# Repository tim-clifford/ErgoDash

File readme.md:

# ErgoDash-R

# Changes from original ErgoDash

- Added rotary encoder (scroll wheel) in place of the ErgoDash's optional outer thumb buttons
- Removed speaker to make pin available for rotary encoder
- Replaced firmware backlight control with physical toggle switch to make pin available for rotary encoder
- Replaced some parts with ones easier to obtain in the UK
- Added jumper pin positions for backlight switch and spare keyboard switch to allow adding functionality later

# Parts

[Parts List](https://github.com/tim-clifford/ErgoDash-R/tree/master/doc/shoplist.ods)

# Firmware

The ErgoDash-R uses QMK for its firmware. It will need updating from the original ErgoDash firmware here:
[QMK - ErgoDash directory](https://github.com/qmk/qmk_firmware/tree/master/keyboards/ergodash)
.  

# Build Guide

I will add a build guide once I have finished building mine! The original ErgoDash build guide is likely to be useful:

[ErgoDash Build Guide](https://github.com/omkbd/ErgoDash/blob/master/Doc/build-en.md)

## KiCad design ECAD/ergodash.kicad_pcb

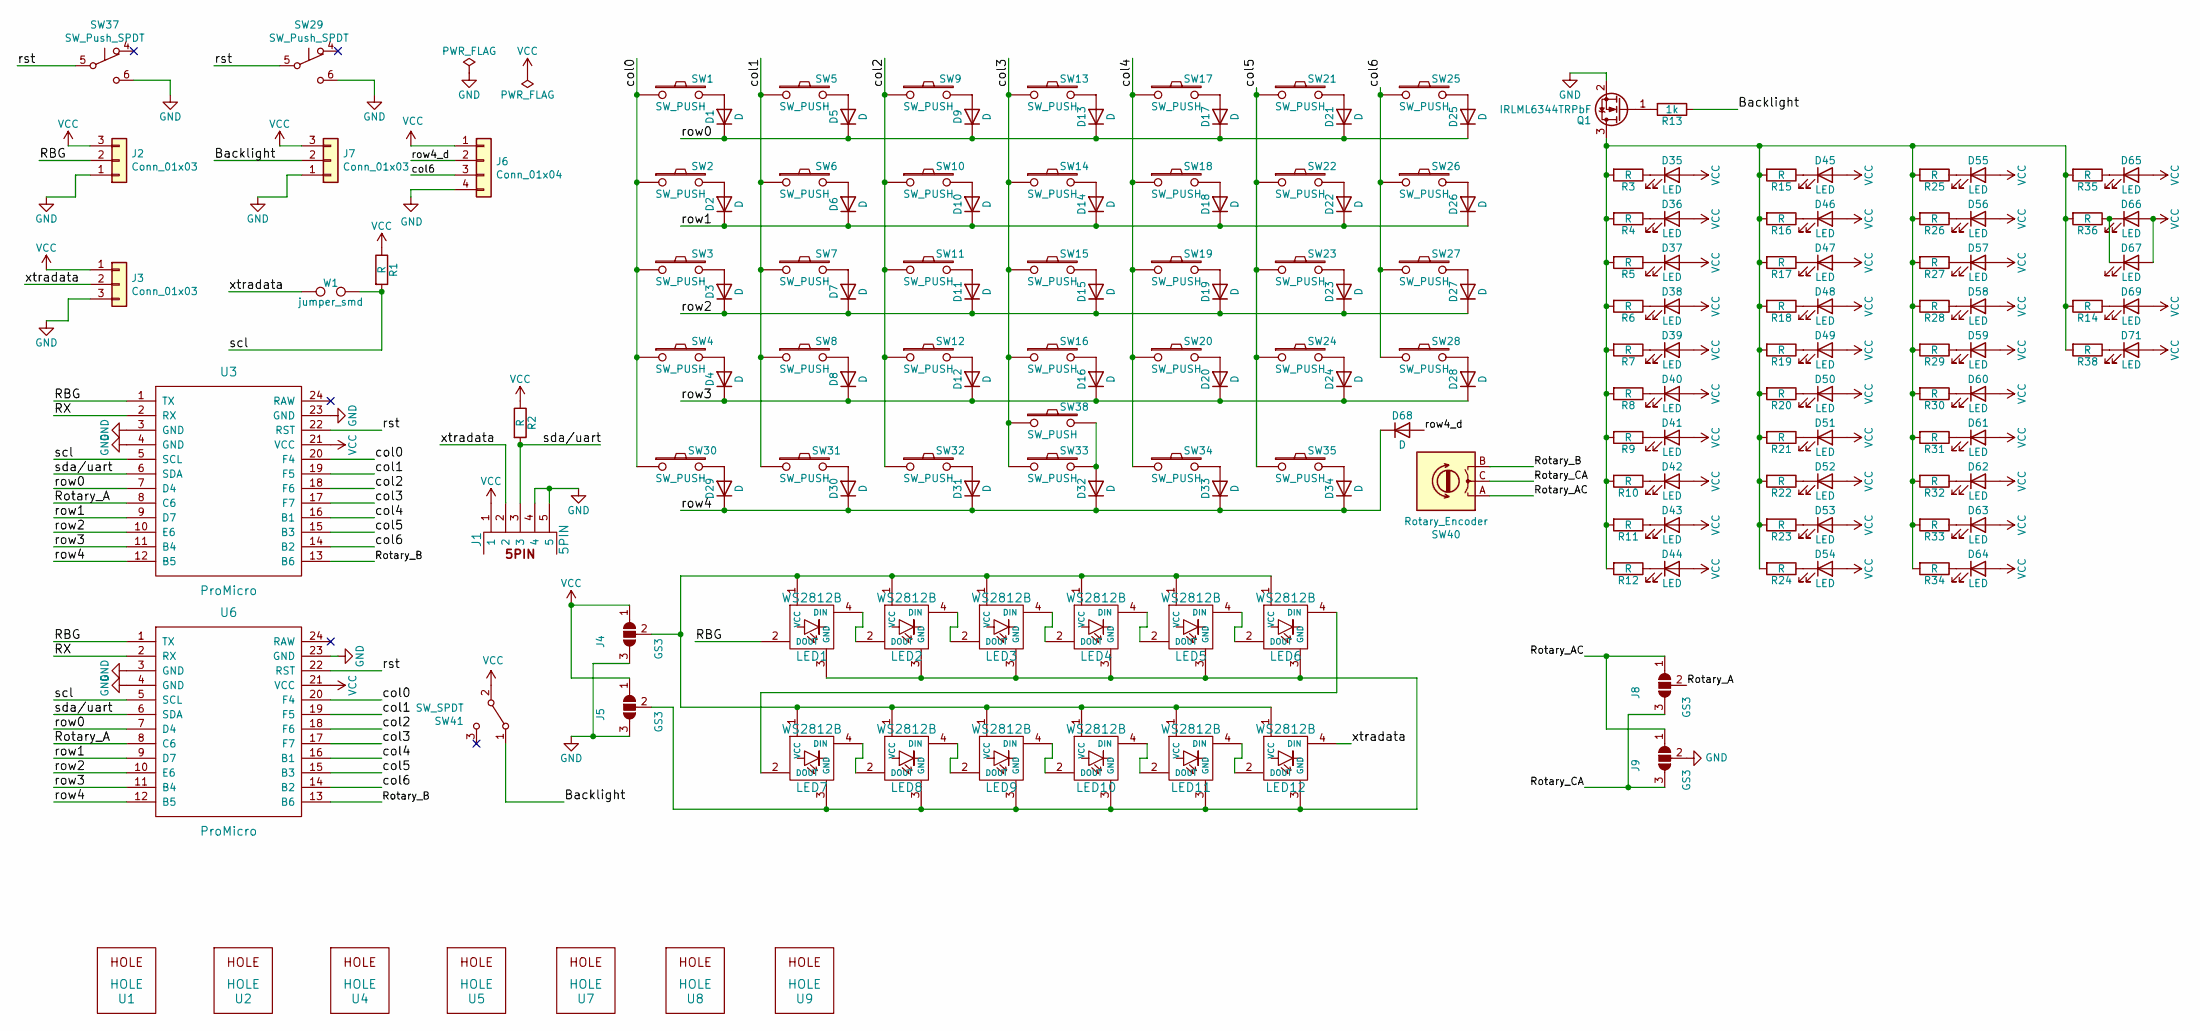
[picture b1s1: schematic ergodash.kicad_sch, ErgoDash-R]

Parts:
D1, D2, D3, D4, D5, D6, D7, D8, D9, D10, D11, D12, D13, D14, D15, D16, D17, D18, D19, D20, D21, D22, D23, D24, D25, D26, D27, D28, D29, D30, D31, D32, D33, D34, D68: D; Diode_SMD_THT3
D35, D36, D37, D38, D39, D40, D41, D42, D43, D44, D45, D46, D47, D48, D49, D50, D51, D52, D53, D54, D55, D56, D57, D58, D59, D60, D61, D62, D63, D64, D65, D66, D67, D69, D71: LED; CHERRY_MX_LED2
J1: 5PIN; trss_jack
J2, J3, J7: Conn_01x03; conn3
J4, J5, J8, J9: GS3; jumper2
J6: Conn_01x04; conn4
LED1, LED2, LED3, LED4, LED5, LED6, LED7, LED8, LED9, LED10, LED11, LED12: WS2812B; WS2812B-5
Q1: IRLML6344TRPbF; SOT-23_2
R1, R2: R; R_Axial_DIN0207_L6.3mm_D2.5mm_P10.16mm_Horizontal
R3, R4, R5, R6, R7, R8, R9, R10, R11, R12, R14, R15, R16, R17, R18, R19, R20, R21, R22, R23, R24, R25, R26, R27, R28, R29, R30, R31, R32, R33, R34, R35, R36, R38: R; Resistors_SMD_THT
R13: 1k; Resistors_SMD_THT
SW1, SW2, SW3, SW4, SW5, SW6, SW7, SW8, SW9, SW10, SW11, SW12, SW13, SW14, SW15, SW16, SW17, SW18, SW19, SW20, SW21, SW22, SW23, SW24, SW25, SW26, SW27, SW28, SW30, SW31, SW32, SW33, SW34, SW35, SW38: SW_PUSH; MX_ALPS
SW29, SW37: SW_Push_SPDT
SW40: Rotary_Encoder; Kailh_Encoder
SW41: SW_SPDT; MC2MS1T2B2M6RE
U1, U2, U4, U5, U7, U8, U9: HOLE; hole
U3, U6: ProMicro
W1: jumper_smd; jumper_smd_2dub

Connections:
/Backlight: J7.2, R13.1, SW41.1 (A)
/RBG: J2.2, LED1.2 (DOUT), U3.1 (TX), U6.1 (TX)
/RX: U3.2 (RX), U6.2 (RX)
/Rotary_A: J8.2 (C), U3.8 (C6), U6.8 (C6)
/Rotary_AC: J8.1 (A), J9.1 (A), SW40.A
/Rotary_B: SW40.B, U3.13 (B6), U6.13 (B6)
/Rotary_CA: J8.3 (B), J9.3 (B), SW40.C
/col0: SW1.1, SW2.1, SW3.1, SW4.1, SW30.1, U3.20 (F4), U6.20 (F4)
/col1: SW5.1, SW6.1, SW7.1, SW8.1, SW31.1, U3.19 (F5), U6.19 (F5)
/col2: SW9.1, SW10.1, SW11.1, SW12.1, SW32.1, U3.18 (F6), U6.18 (F6)
/col3: SW13.1, SW14.1, SW15.1, SW16.1, SW33.1, SW38.1, U3.17 (F7), U6.17 (F7)
/col4: SW17.1, SW18.1, SW19.1, SW20.1, SW34.1, U3.16 (B1), U6.16 (B1)
/col5: SW21.1, SW22.1, SW23.1, SW24.1, SW35.1, U3.15 (B3), U6.15 (B3)
/col6: J6.3, SW25.1, SW26.1, SW27.1, SW28.1, U3.14 (B2), U6.14 (B2)
/row0: D1.1 (K), D5.1 (K), D9.1 (K), D13.1 (K), D17.1 (K), D21.1 (K), D25.1 (K), U3.7 (D4), U6.7 (D4)
/row1: D2.1 (K), D6.1 (K), D10.1 (K), D14.1 (K), D18.1 (K), D22.1 (K), D26.1 (K), U3.9 (D7), U6.9 (D7)
/row2: D3.1 (K), D7.1 (K), D11.1 (K), D15.1 (K), D19.1 (K), D23.1 (K), D27.1 (K), U3.10 (E6), U6.10 (E6)
/row3: D4.1 (K), D8.1 (K), D12.1 (K), D16.1 (K), D20.1 (K), D24.1 (K), D28.1 (K), U3.11 (B4), U6.11 (B4)
/row4: D29.1 (K), D30.1 (K), D31.1 (K), D32.1 (K), D33.1 (K), D34.1 (K), D68.1 (K), U3.12 (B5), U6.12 (B5)
/row4_d: D68.2 (A), J6.2
/rst: SW29.5 (B), SW37.5 (B), U3.22 (RST), U6.22 (RST)
/scl: R1.2, U3.5 (SCL), U6.5 (SCL), W1.2
/sda/uart: J1.3, R2.2, U3.6 (SDA), U6.6 (SDA)
/xtradata: J1.2, J3.2, LED12.4 (DIN), W1.1
GND: J1.4, J1.5, J2.1, J3.3, J4.3 (B), J5.3 (B), J6.4, J7.1, J9.2 (C), Q1.2 (S), SW29.6 (C), SW37.6 (C), U3.3 (GND), U3.4 (GND), U3.23 (GND), U6.3 (GND), U6.4 (GND), U6.23 (GND)
unnamed: D1.2 (A), SW1.2
unnamed: D2.2 (A), SW2.2
unnamed: D3.2 (A), SW3.2
unnamed: D4.2 (A), SW4.2
unnamed: D5.2 (A), SW5.2
unnamed: D6.2 (A), SW6.2
unnamed: D7.2 (A), SW7.2
unnamed: D8.2 (A), SW8.2
unnamed: D9.2 (A), SW9.2
unnamed: D10.2 (A), SW10.2
unnamed: D11.2 (A), SW11.2
unnamed: D12.2 (A), SW12.2
unnamed: D13.2 (A), SW13.2
unnamed: D14.2 (A), SW14.2
unnamed: D15.2 (A), SW15.2
unnamed: D16.2 (A), SW16.2
unnamed: D17.2 (A), SW17.2
unnamed: D18.2 (A), SW18.2
unnamed: D19.2 (A), SW19.2
unnamed: D20.2 (A), SW20.2
unnamed: D21.2 (A), SW21.2
unnamed: D22.2 (A), SW22.2
unnamed: D23.2 (A), SW23.2
unnamed: D24.2 (A), SW24.2
unnamed: D25.2 (A), SW25.2
unnamed: D26.2 (A), SW26.2
unnamed: D27.2 (A), SW27.2
unnamed: D28.2 (A), SW28.2
unnamed: D29.2 (A), SW30.2
unnamed: D30.2 (A), SW31.2
unnamed: D31.2 (A), SW32.2
unnamed: D32.2 (A), SW33.2, SW38.2
unnamed: D33.2 (A), SW34.2
unnamed: D34.2 (A), SW35.2
unnamed: D35.1 (K), R3.1
unnamed: D36.1 (K), R4.1
unnamed: D37.1 (K), R5.1
unnamed: D38.1 (K), R6.1
unnamed: D39.1 (K), R7.1
unnamed: D40.1 (K), R8.1
unnamed: D41.1 (K), R9.1
unnamed: D42.1 (K), R10.1
unnamed: D43.1 (K), R11.1
unnamed: D44.1 (K), R12.1
unnamed: D45.1 (K), R15.1
unnamed: D46.1 (K), R16.1
unnamed: D47.1 (K), R17.1
unnamed: D48.1 (K), R18.1
unnamed: D49.1 (K), R19.1
unnamed: D50.1 (K), R20.1
unnamed: D51.1 (K), R21.1
unnamed: D52.1 (K), R22.1
unnamed: D53.1 (K), R23.1
unnamed: D54.1 (K), R24.1
unnamed: D55.1 (K), R25.1
unnamed: D56.1 (K), R26.1
unnamed: D57.1 (K), R27.1
unnamed: D58.1 (K), R28.1
unnamed: D59.1 (K), R29.1
unnamed: D60.1 (K), R30.1
unnamed: D61.1 (K), R31.1
unnamed: D62.1 (K), R32.1
unnamed: D63.1 (K), R33.1
unnamed: D64.1 (K), R34.1
unnamed: D65.1 (K), R35.1
unnamed: D66.1 (K), D67.1 (K), R36.1
unnamed: D69.1 (K), R14.1
unnamed: D71.1 (K), R38.1
unnamed: J4.2 (C), LED1.1 (VCC), LED2.1 (VCC), LED3.1 (VCC), LED4.1 (VCC), LED5.1 (VCC), LED6.1 (VCC), LED7.1 (VCC), LED8.1 (VCC), LED9.1 (VCC), LED10.1 (VCC), LED11.1 (VCC), LED12.1 (VCC)
unnamed: J5.2 (C), LED1.3 (GND), LED2.3 (GND), LED3.3 (GND), LED4.3 (GND), LED5.3 (GND), LED6.3 (GND), LED7.3 (GND), LED8.3 (GND), LED9.3 (GND), LED10.3 (GND), LED11.3 (GND), LED12.3 (GND)
unnamed: LED1.4 (DIN), LED2.2 (DOUT)
unnamed: LED2.4 (DIN), LED3.2 (DOUT)
unnamed: LED3.4 (DIN), LED4.2 (DOUT)
unnamed: LED4.4 (DIN), LED5.2 (DOUT)
unnamed: LED5.4 (DIN), LED6.2 (DOUT)
unnamed: LED6.4 (DIN), LED7.2 (DOUT)
unnamed: LED7.4 (DIN), LED8.2 (DOUT)
unnamed: LED8.4 (DIN), LED9.2 (DOUT)
unnamed: LED9.4 (DIN), LED10.2 (DOUT)
unnamed: LED10.4 (DIN), LED11.2 (DOUT)
unnamed: LED11.4 (DIN), LED12.2 (DOUT)
unnamed: Q1.1 (G), R13.2
unnamed: Q1.3 (D), R3.2, R4.2, R5.2, R6.2, R7.2, R8.2, R9.2, R10.2, R11.2, R12.2, R14.2, R15.2, R16.2, R17.2, R18.2, R19.2, R20.2, R21.2, R22.2, R23.2, R24.2, R25.2, R26.2, R27.2, R28.2, R29.2, R30.2, R31.2, R32.2, R33.2, R34.2, R35.2, R36.2, R38.2
VCC: D35.2 (A), D36.2 (A), D37.2 (A), D38.2 (A), D39.2 (A), D40.2 (A), D41.2 (A), D42.2 (A), D43.2 (A), D44.2 (A), D45.2 (A), D46.2 (A), D47.2 (A), D48.2 (A), D49.2 (A), D50.2 (A), D51.2 (A), D52.2 (A), D53.2 (A), D54.2 (A), D55.2 (A), D56.2 (A), D57.2 (A), D58.2 (A), D59.2 (A), D60.2 (A), D61.2 (A), D62.2 (A), D63.2 (A), D64.2 (A), D65.2 (A), D66.2 (A), D67.2 (A), D69.2 (A), D71.2 (A), J1.1, J2.3, J3.1, J4.1 (A), J5.1 (A), J6.1, J7.3, R1.1, R2.1, SW41.2 (B), U3.21 (VCC), U6.21 (VCC)
no_connect_110: SW29.4 (A)
no_connect_111: SW37.4 (A)
no_connect_112: SW41.3 (C)
no_connect_113: U3.24 (RAW)
no_connect_114: U6.24 (RAW)

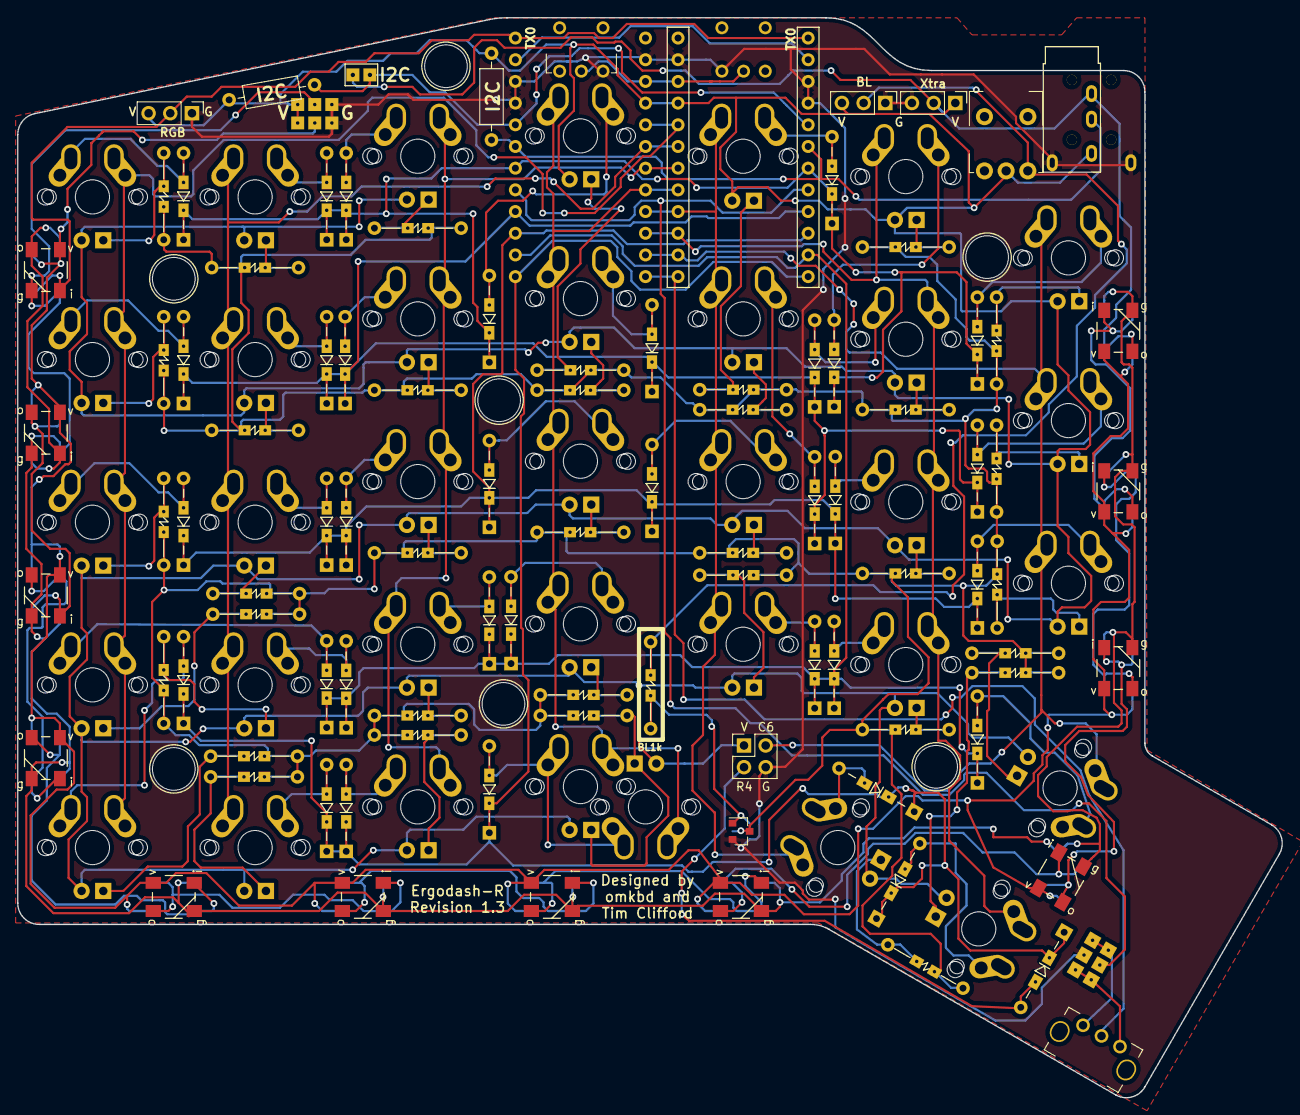
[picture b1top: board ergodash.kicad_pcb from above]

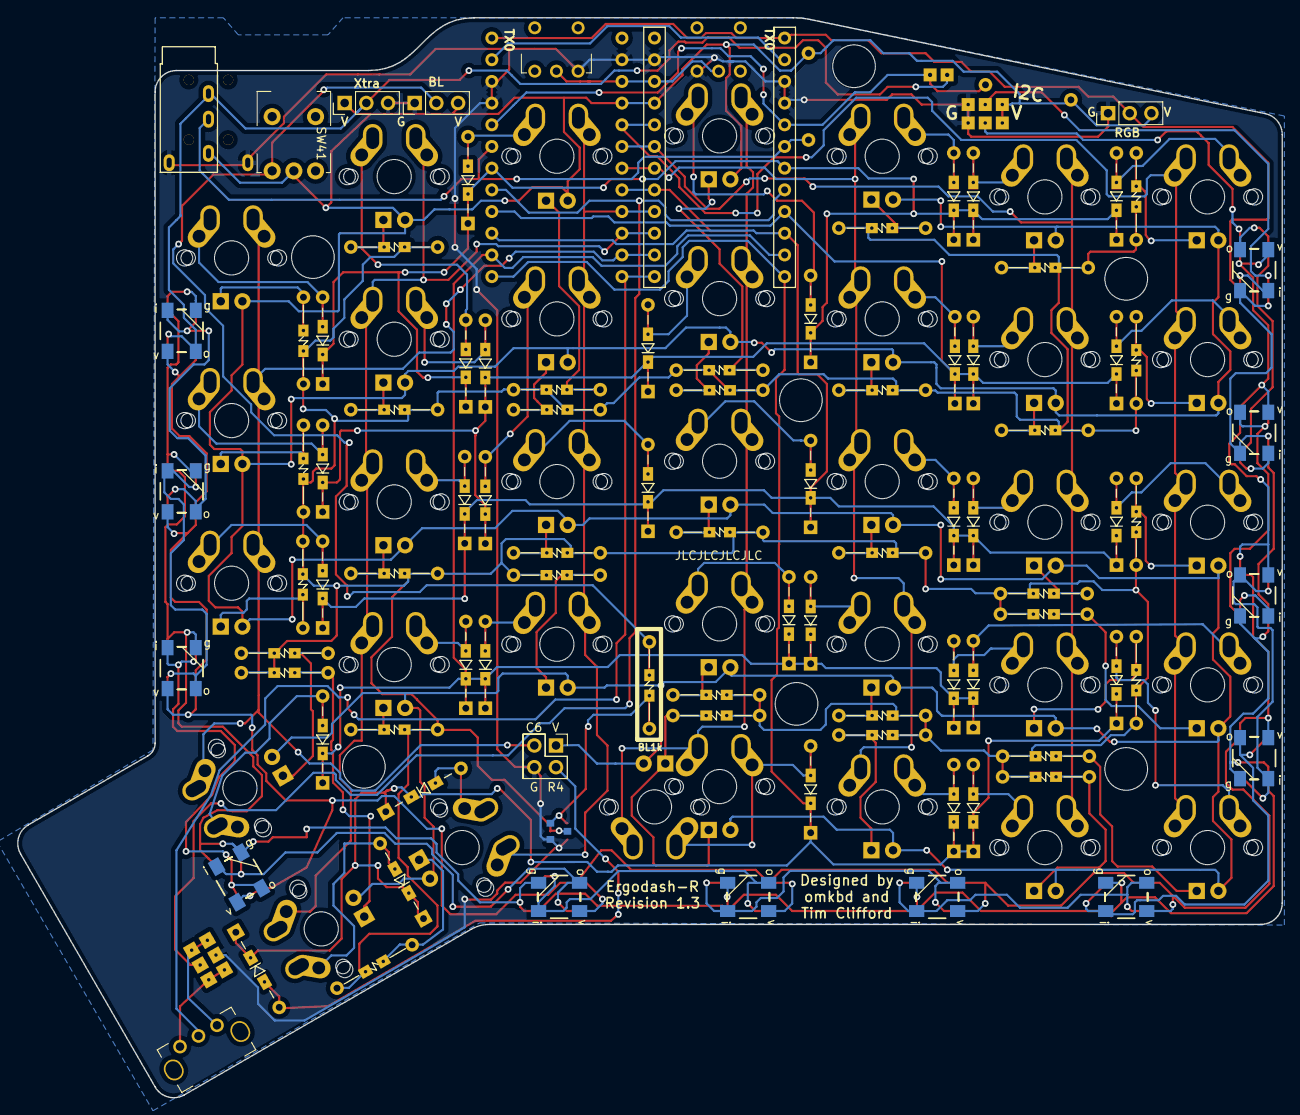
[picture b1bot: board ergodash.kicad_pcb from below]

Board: 2 copper layers, 148.1 x 126.5 mm, 178 parts (28 on the bottom side), 109 nets.

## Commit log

2020-12-17 Increase thickness of connection to optional thumb pads and update EESchema symbols
2020-12-17 Convert to Kicad 6
2020-12-29 ErgoDash-R
